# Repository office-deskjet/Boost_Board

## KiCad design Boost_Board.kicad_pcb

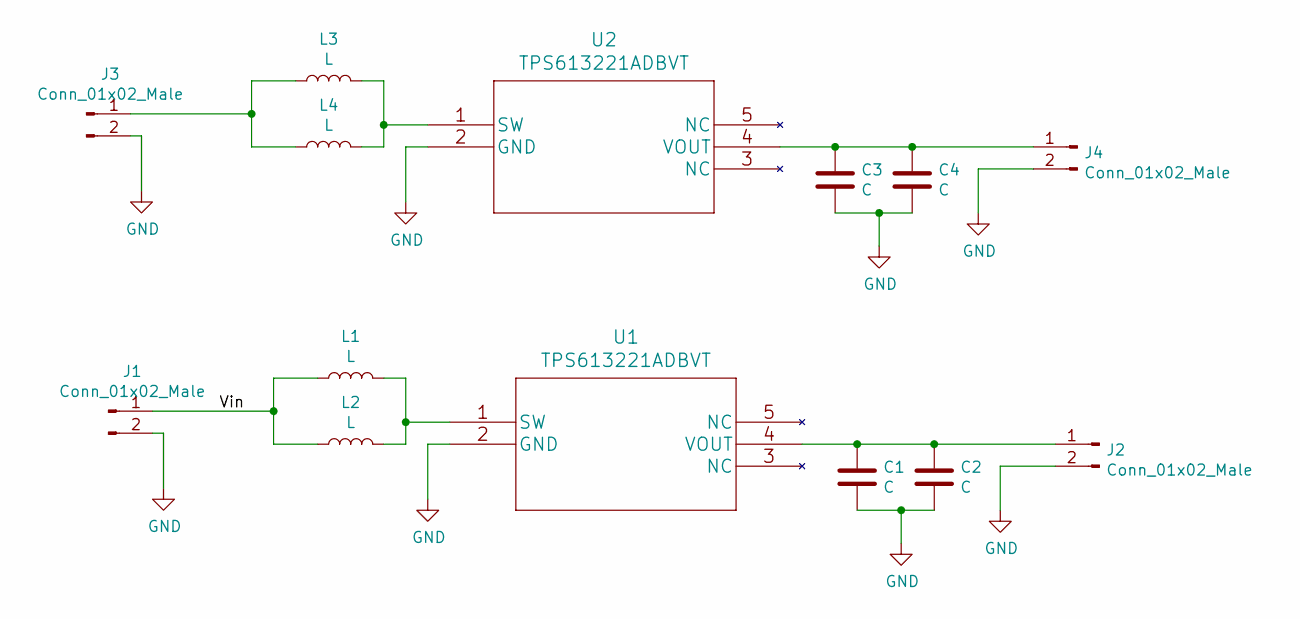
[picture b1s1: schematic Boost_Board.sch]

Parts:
C1, C2, C3, C4: C; C_0805_2012Metric_Pad1.15x1.40mm_HandSolder
J1, J2, J3, J4: Conn_01x02_Male; PinHeader_1x02_P2.54mm_Vertical
L1, L3: L; L_0805_2012Metric_Pad1.15x1.40mm_HandSolder
L2, L4: L; 1008_Inductor
U1, U2: TPS613221ADBVT; SOT-23-5_HandSoldering

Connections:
/Vin: J1.1, L1.1, L2.1
GND: C1.2, C2.2, C3.2, C4.2, J1.2, J2.2, J3.2, J4.2, U1.2 (GND), U2.2 (GND)
unnamed: C1.1, C2.1, J2.1, U1.4 (VOUT)
unnamed: C3.1, C4.1, J4.1, U2.4 (VOUT)
unnamed: J3.1, L3.1, L4.1
unnamed: L1.2, L2.2, U1.1 (SW)
unnamed: L3.2, L4.2, U2.1 (SW)

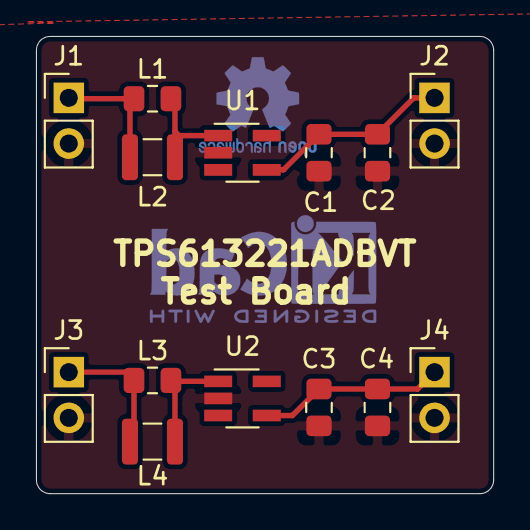
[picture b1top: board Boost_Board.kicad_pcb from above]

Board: 2 copper layers, 25.4 x 25.4 mm, 14 parts (0 on the bottom side), 7 nets.

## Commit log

2019-06-17 KiCad Files. Adding schematic
2019-06-17 done with layout
